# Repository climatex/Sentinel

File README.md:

# Project Sentinel, an RPi Pico 2 MFM/RLL disk controller
Check out my [website article](https://boginjr.com/it/hw/sentinel) to learn more!

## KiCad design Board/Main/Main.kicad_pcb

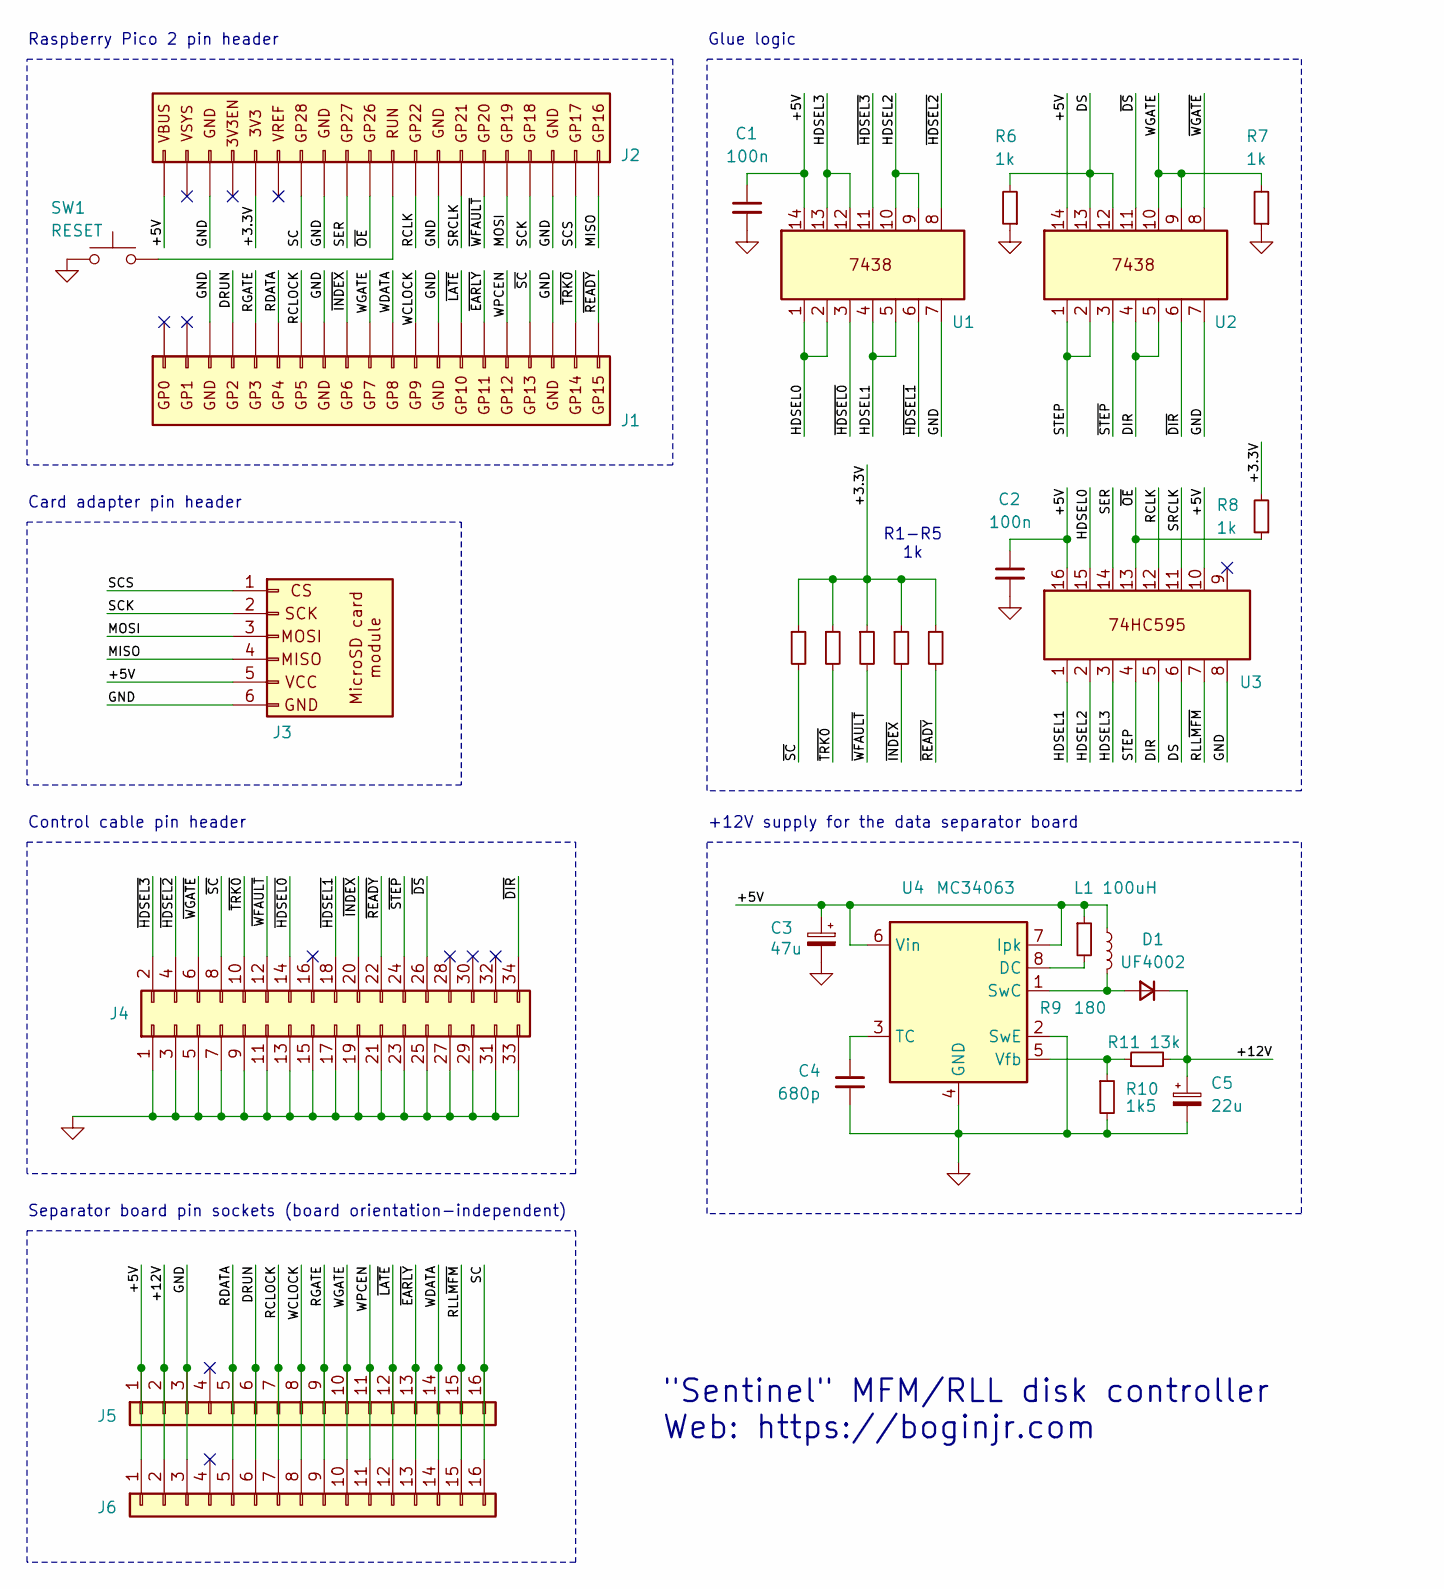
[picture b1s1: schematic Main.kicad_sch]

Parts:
C1, C2: 100n; C_Disc_D7.5mm_W2.5mm_P5.00mm
C3: 47u; CP_Radial_D6.3mm_P2.50mm
C4: 680p; C_Disc_D7.5mm_W2.5mm_P5.00mm
C5: 22u; CP_Radial_D6.3mm_P2.50mm
D1: UF4002; D_DO-41_SOD81_P10.16mm_Horizontal
J1, J2: Conn_01x20; PinSocket_1x20_P2.54mm_Vertical
J3: Digital; PinHeader_1x06_P2.54mm_Vertical
J4: PinHeader_2x17_P2.54mm_Vertical
J5, J6: Conn_01x16; PinSocket_1x16_P2.54mm_Vertical
L1: 100uH; L_Radial_D8.7mm_P5.00mm_Fastron_07HCP
R1, R2, R3, R4, R5: 10K; R_Axial_DIN0207_L6.3mm_D2.5mm_P10.16mm_Horizontal
R6, R7, R8: 1k; R_Axial_DIN0207_L6.3mm_D2.5mm_P10.16mm_Horizontal
R9: 180; R_Axial_DIN0207_L6.3mm_D2.5mm_P10.16mm_Horizontal
R10: 1k5; R_Axial_DIN0207_L6.3mm_D2.5mm_P10.16mm_Horizontal
R11: 13k; R_Axial_DIN0207_L6.3mm_D2.5mm_P10.16mm_Horizontal
SW1: RESET; SW_PUSH_6mm
U1, U2: DIP-14_W7.62mm_LongPads
U3: DIP-16_W7.62mm_LongPads
U4: MC34063; DIP-8_W7.62mm_LongPads

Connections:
/+3.3V: J2.16, R1.1, R2.1, R3.1, R4.1, R5.1, R8.2
/+5V: C1.1, C2.1, C3.1, J2.20, J3.5, J5.1, J6.1, L1.1, R9.1, U1.14, U2.14, U3.10, U3.16, U4.6 (Vin), U4.7 (Ipk)
/+12V: C5.1, D1.1 (K), J5.2, J6.2, R11.2
/DIR: U2.4, U2.5, U3.5
/DRUN: J1.4, J5.6, J6.6
/DS: R6.2, U2.12, U2.13, U3.6
/HDSEL0: U1.1, U1.2, U3.15
/HDSEL1: U1.4, U1.5, U3.1
/HDSEL2: U1.9, U1.10, U3.2
/HDSEL3: U1.12, U1.13, U3.3
/MISO: J2.1, J3.4
/MOSI: J2.5, J3.3
/RCLK: J2.9, U3.12
/RCLOCK: J1.7, J5.7, J6.7
/RDATA: J1.6, J5.5, J6.5
/RGATE: J1.5, J5.9, J6.9
/RLL~MFM: J5.15, J6.15, U3.7
/SC: J2.14, J5.16, J6.16
/SCK: J2.4, J3.2
/SCS: J2.2, J3.1
/SER: J2.12, U3.14
/SRCLK: J2.7, U3.11
/STEP: U2.1, U2.2, U3.4
/WCLOCK: J1.12, J5.8, J6.8
/WDATA: J1.11, J5.14, J6.14
/WGATE: J1.10, J5.10, J6.10, R7.2, U2.9, U2.10
/WPCEN: J1.16, J5.11, J6.11
/~DIR: J4.34, U2.6
/~DS: J4.26, U2.11
/~EARLY: J1.15, J5.13, J6.13
/~HDSEL0: J4.14, U1.3
/~HDSEL1: J4.18, U1.6
/~HDSEL2: J4.4, U1.8
/~HDSEL3: J4.2, U1.11
/~INDEX: J1.9, J4.20, R4.2
/~LATE: J1.14, J5.12, J6.12
/~OE: J2.11, R8.1, U3.13
/~READY: J1.20, J4.22, R5.2
/~SC: J1.17, J4.8, R1.2
/~STEP: J4.24, U2.3
/~TRK0: J1.19, J4.10, R2.2
/~WFAULT: J2.6, J4.12, R3.2
/~WGATE: J4.6, U2.8
GND: C1.2, C2.2, C3.2, C4.2, C5.2, J1.3, J1.8, J1.13, J1.18, J2.3, J2.8, J2.13, J2.18, J3.6, J4.1, J4.3, J4.5, J4.7, J4.9, J4.11, J4.13, J4.15, J4.17, J4.19, J4.21, J4.23, J4.25, J4.27, J4.29, J4.31, J4.33, J5.3, J6.3, R6.1, R7.1, R10.2, SW1.2, U1.7, U2.7, U3.8, U4.2 (SwE), U4.4 (GND)
unnamed: D1.2 (A), L1.2, U4.1 (SwC)
unnamed: J2.10, SW1.1
unnamed: R9.2, U4.8 (DC)
unnamed: C4.1, U4.3 (TC)
unnamed: R10.1, R11.1, U4.5 (Vfb)

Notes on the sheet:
Card adapter pin header
Raspberry Pico 2 pin header
Control cable pin header
Glue logic
"Sentinel" MFM/RLL disk controller Web: https://boginjr.com
Separator board pin sockets (board orientation-independent)
+12V supply for the data separator board
R1-R5 1k

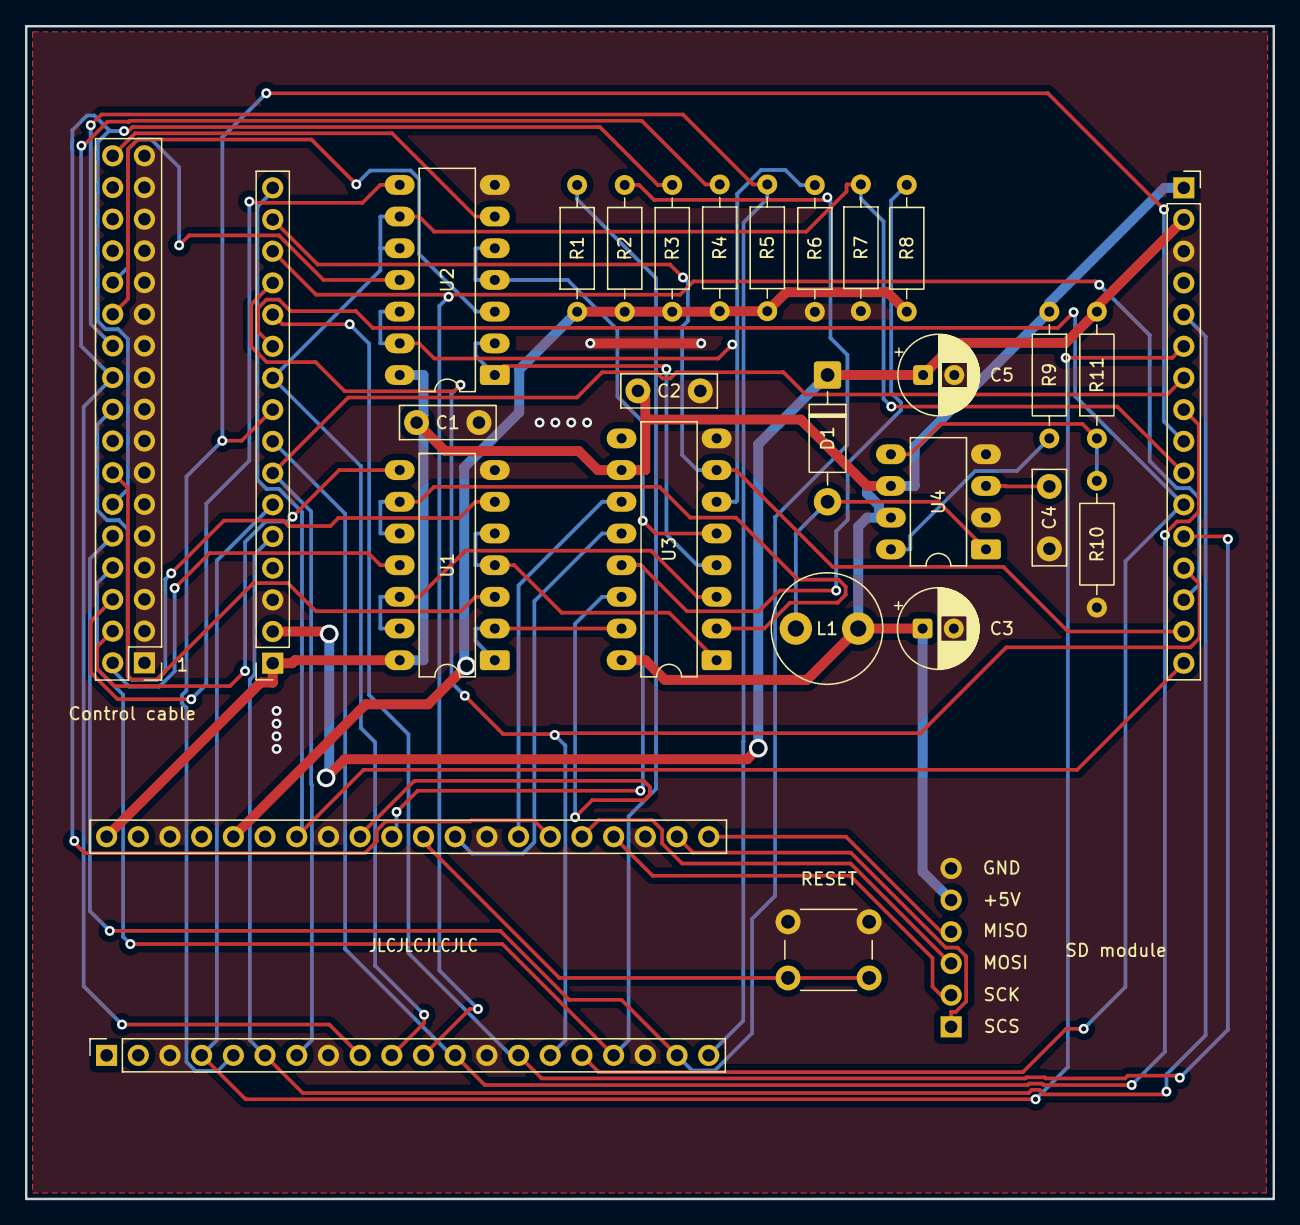
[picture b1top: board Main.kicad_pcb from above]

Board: 2 copper layers, 100.0 x 94.0 mm, 29 parts (1 on the bottom side), 49 nets.

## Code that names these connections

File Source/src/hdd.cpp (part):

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  // m_ShiftRegister bits 7-0:
  // /MFM, DS, DIR, STEP, HDSEL3, HDSEL2, HDSEL1, HDSEL0
  
  gpio_put(22, false);  // RCLK low
  uint8_t bit = 8;
  while (bit--)
  {
    // set SER
    gpio_put(27, m_ShiftRegister & (1 << bit));    
    gpio_put(21, true); // toggle SRCLK
    busy_wait_at_least_cycles(80);
    gpio_put(21, false);
    busy_wait_at_least_cycles(80);
  }  
  
  gpio_put(22, true);   // RCLK high
}

void HDD::selectDrive(bool ds0 /* = true */)
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    }
  }
  
  return gpio_get(20); // to be considered ready, /WFAULT must be also high
}

bool HDD::isAtCylinder0()
{
  return !gpio_get(14); // /TRK0
}

bool HDD::checkReadyWriteFault()
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  {
    if (m_PhysicalCylinder >= m_Params.RWCStartCyl)
    {
      m_ShiftRegister |= 8;    // HDSEL3 high (low /REDWC on drive)
    }
    else
    {
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  {
    if (m_PhysicalCylinder >= m_Params.WritePrecompStartCyl)
    {
      gpio_put(12, true);      // WPCEN
    }
    else
    {
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
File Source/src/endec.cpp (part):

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{
  // assert RGATE and begin reading once DRUN circuit detects preambles (zeros)
  const absolute_time_t deadline = make_timeout_time_us(timeout_us);
  while (!gpio_get(2)) // DRUN
  {
    if (time_reached(deadline))
    {
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         (startOfTrack || gpio_get(6)) &&
         !pio_sm_is_tx_fifo_empty(pio0, 1))
  {
    if (gpio_get(6)) // /INDEX went high, reset start of track flag
    {
      startOfTrack = false;
    }
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uint8_t ENDEC::getPrecompNibble(bool wdata, Precomp precomp)
{
  // prepare a 4-bit nibble containing write and precompensation information
  // bits 3-0: /EARLY, /LATE, unused, WDATA -> to be routed to GPIO 11, 10, 9, 8 in this order
  
  if (!wdata) // transition
  {
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     
  for (size_t i = 0; i < rllBitCount; i++)
  {
    const bool wdata = getBit(rllBytes.data(), rllBytes.size(), i);
    Precomp precomp = PRECOMP_NOMINAL;
 
    if (wdata)
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
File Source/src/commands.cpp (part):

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  }  
  hdd.selectDrive(false);
  
  const uint16_t nominalTrackBytes = (uint16_t)((g_WclockRate * 16666.67) / 8.0) * 2; // x2, sampling both RCLOCK/WCLOCK edges
  printf(str_RawdiskTrackLength, nominalTrackBytes, str_Bytes);
  
  // ask to customize maximum number of bytes read
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        // apply write precompensation for an already encoded bitstream
        for (size_t i = 0; i < bitsTotal; i++)
        {         
          const bool wdata = endec.getBit(trackBuffer.data(), bytesOkay, i);
          ENDEC::Precomp precomp = ENDEC::PRECOMP_NOMINAL; // default
          
          if (wdata)
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               (writeIgnoreIndex || (startOfTrack || gpio_get(6))) &&
               !pio_sm_is_tx_fifo_empty(pio0, 1))
        {
          if (gpio_get(6)) // /INDEX went high, reset start of track flag
          {
            startOfTrack = false;
          }
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           gpio_get(20) &&
           (startOfTrack || gpio_get(6)))
    {
      if (gpio_get(6)) // /INDEX went high, reset start of track flag
      {
        startOfTrack = false;
      }
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

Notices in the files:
Source/src/commands.cpp:
Sentinel (c) 2026 J. Bogin, https://boginjr.com
